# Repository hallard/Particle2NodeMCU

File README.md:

Particle Spark/Photon to NodeMCU Adapter
========================================

This adapter is used to put in place of a Spark/Photon a NodeMCU board with ESP8266 I needed for a specific French [project][3]. I needed SPI for RFM69 Module with IRQ on ~~GPIO2~~ GPIO15 and SS on GPIO2 (see below why).
I choosed NodeMCU boards instead of ESP8266 because NodeMCU has all I needed on board, such as pullups, switches, USB power, 3/3V regulator, USB2Serial...

Since ESP8266 has less pin than Particle boards, only "classic" have been connected

- SPI Interface (GPIO12 to 14) GPIO15 is used for RFM69 IRQ
- I2C Interface (GPIO14 and GPIO5)
- Serial (GPIO1 and GPIO3)
- GPIO0 as free I/O (Flash button on NodeMCU)
- GPIO2 is used as Chip Select (SS) for RFM69
- GPIO16 as free I/O (LED and KEY on NodeMCU)

I discovered some issue with 1st design, see below :
- ESP8266 to boot correctly needs some pins at defined level, GPIO15 must be LOW and GPIO2 must be HIGH. Unfortunatlly with RFM69 connected as IRQ to GPIO2 and SS to GPIO15 it does not boot because RF69 pull it DIO IRQ to LOW, making GPIO2 LOW and ESP8266 not booting. The fix is to reverse the wiring, connect IRQ to GPIO15 and SS to GPIO2 (and do according changes in the code). 
- Teleinfo had some issue due to NodeMCU USB/Serial onboard converter that was in conflict and was killing RX signal coming from optocoupler. To avoid this I've put 2 inverters to have a correct RX Teleinfo signal coming to EMP8266. No Risk because on board RX Signal of NodeMCU has a 470 Ohm resistor in serial of this line. To avoid this may be we could use a ESP8266 without any USB/Serial adapteur such as a Adafruit [Huzzah][5] or Olimex [ESP8266 Dev][6]
- it really just to fit board adapter on Remora if you have the big relay installed, it fits but it's really really close, so in version 1.1a, I just moved a little bit the adapter from the board relay.
- to be able to handle future Remora PCB version I added the feature to enable/disable Téléinfo FET Staging (they will already be placed on Remora V1.3 PCB) using Jumper J1 & J2.

This page has been updated to reflect the changes and the PCB also, it's now v1.1a.   

*Boards are still in progress, I did not fully tested them yet, I will update as soon has I got them in my hands. Use at your own risks*

Detailed Description
====================

Look at the schematics for more informations.

### Schematic  

### Boards  
&nbsp;
&nbsp; 

If you have old version V1.0 PCB and a RFM69 attached, here the fix, cut line in red and solder wire on green line.   

&nbsp;
&nbsp; 

You can order the PCB of this board v1.1a at [OSHPARK][4]

### Assembled boards

~~I'm currently waiting for boards from OSHPARK~~
Boards arrived, still testing before ordering V1.1a boards

##License

You can do whatever you like with this design.

##Misc
See news and other projects on my [blog][2] 
 
[2]: https://hallard.me
[3]: https://github.com/thibdct/programmateur-fil-pilote-wifi/tree/master/Logiciel/remora
[4]: https://oshpark.com/shared_projects/jYm6pI7a
[5]: https://www.adafruit.com/product/2471
[6]: https://www.olimex.com/Products/IoT/MOD-WIFI-ESP8266-DEV/

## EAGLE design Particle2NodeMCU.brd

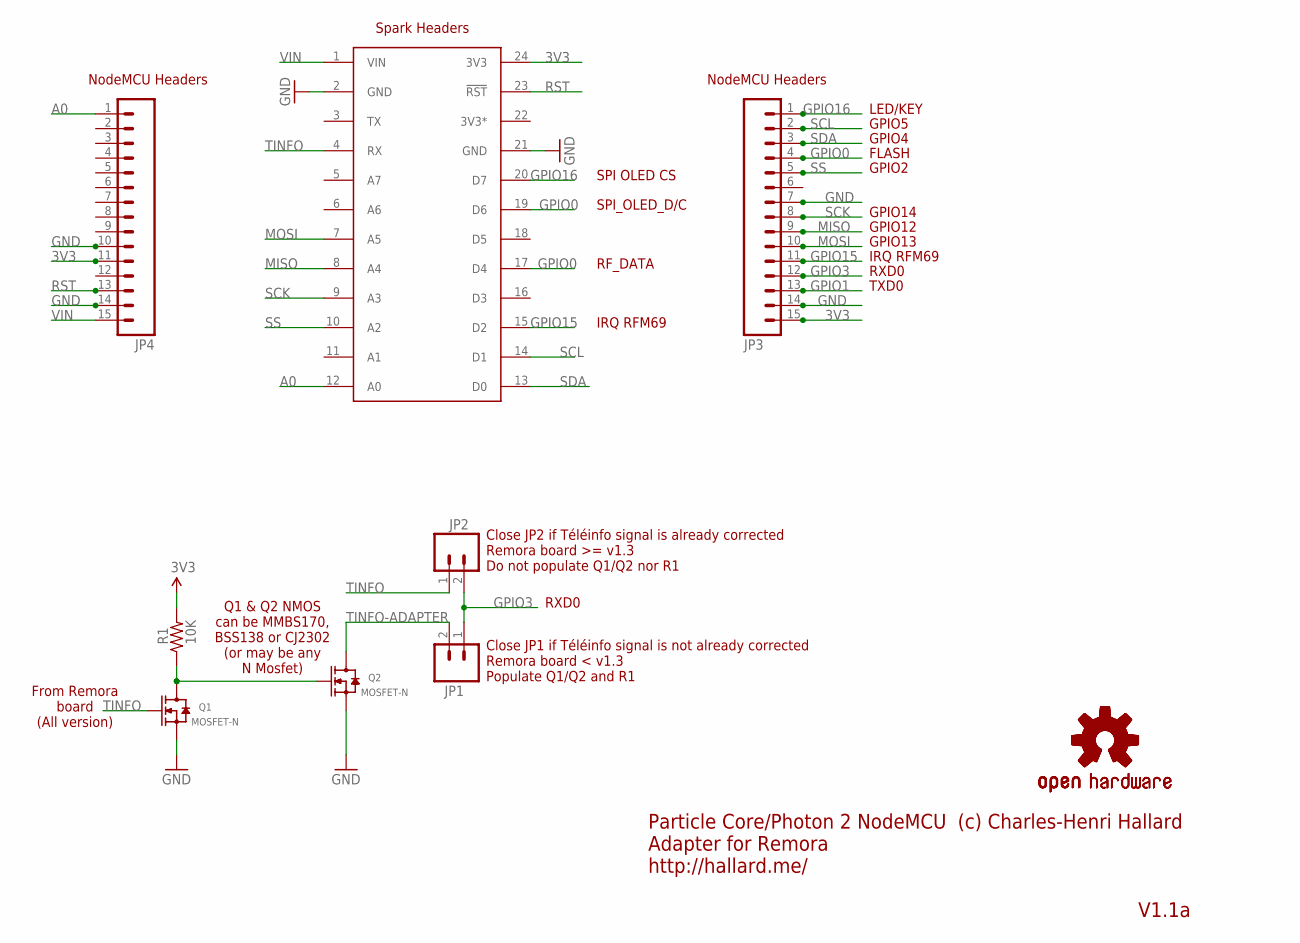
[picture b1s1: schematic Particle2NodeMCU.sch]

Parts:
JP1, JP2: M02LOCK; 1X02_LOCK
JP3, JP4: M15; 1X15
LOGO1, LOGO2: OSHW-LOGOM; OSHW-LOGO-M
Q1, Q2: MOSFET-N; SOT23
R1: 10K; 0805-RES
U$2: SPARK_CORECORE; SPARK_CORE

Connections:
3V3: JP3.15, JP4.11, R1.2, U$2.24 (3V3)
3V3*: U$2.22 (3V3*)
A0: JP4.1, U$2.12 (A0)
GND: JP3.7, JP3.14, JP4.10, JP4.14, Q1.2 (S), Q2.2 (S), U$2.2 (GND), U$2.21 (GND)
GPIO0: JP3.4, U$2.17 (D4), U$2.19 (D6)
GPIO1: JP3.13
GPIO3: JP1.1, JP2.2, JP3.12
GPIO15: JP3.11, U$2.15 (D2)
GPIO16: JP3.1, U$2.20 (D7)
MISO: JP3.9, U$2.8 (A4)
MOSI: JP3.10, U$2.7 (A5)
unnamed: Q1.3 (D), Q2.1 (G), R1.1
RST: JP4.13, U$2.23 (!RST)
SCK: JP3.8, U$2.9 (A3)
SCL: JP3.2, U$2.14 (D1)
SDA: JP3.3, U$2.13 (D0)
SS: JP3.5, U$2.10 (A2)
TINFO: JP2.1, Q1.1 (G), U$2.4 (RX)
TINFO-ADAPTER: JP1.2, Q2.3 (D)
VIN: JP4.15, U$2.1 (VIN)

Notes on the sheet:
IRQ RFM69
FLASH
GPIO12
GPIO4
GPIO5
RXD0
TXD0
GPIO13
GPIO14
GPIO2
LED/KEY
NodeMCU Headers
SPI_OLED_D/C
SPI OLED CS
RF_DATA
Spark Headers
Particle Core/Photon 2 NodeMCU Adapter for Remora http://hallard.me/
(c) Charles-Henri Hallard
V1.1a
Q1 & Q2 NMOS can be MMBS170, BSS138 or CJ2302 (or may be any N Mosfet)
Close JP1 if Téléinfo signal is not already corrected Remora board < v1.3 Populate Q1/Q2 and R1
Close JP2 if Téléinfo signal is already corrected Remora board >= v1.3 Do not populate Q1/Q2 nor R1
From Remora board (All version)

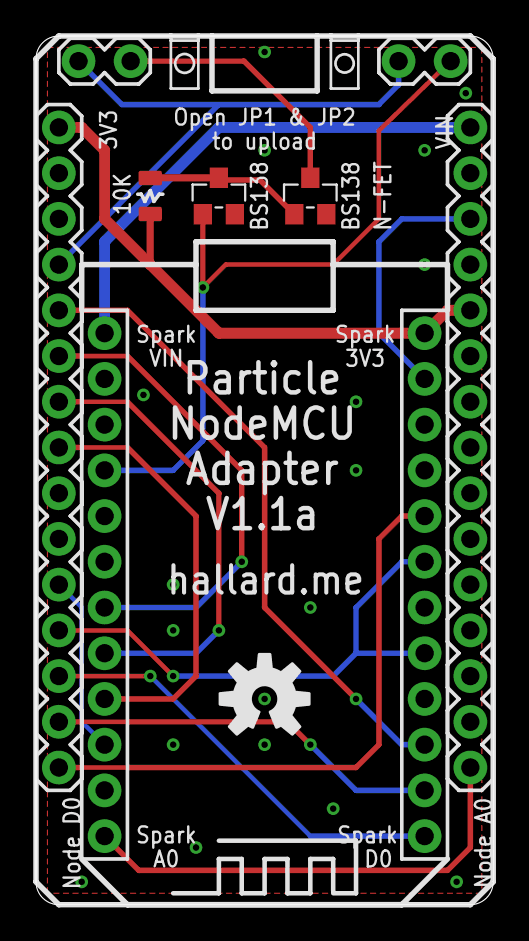
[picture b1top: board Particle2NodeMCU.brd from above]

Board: 2 copper layers, 25.4 x 48.3 mm, 10 parts (1 on the bottom side), 18 nets.

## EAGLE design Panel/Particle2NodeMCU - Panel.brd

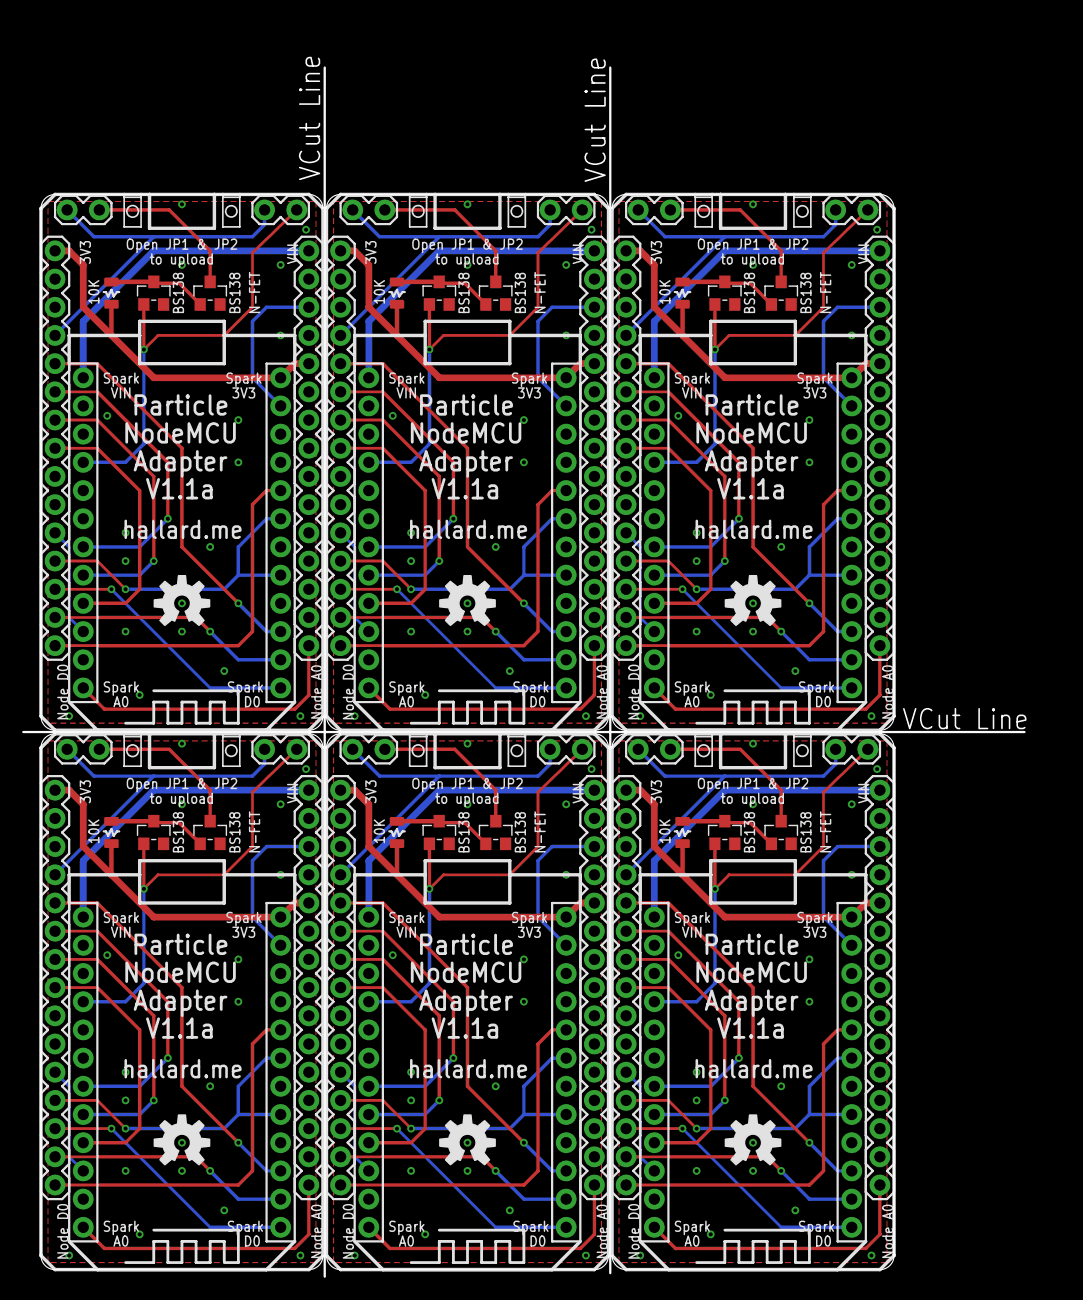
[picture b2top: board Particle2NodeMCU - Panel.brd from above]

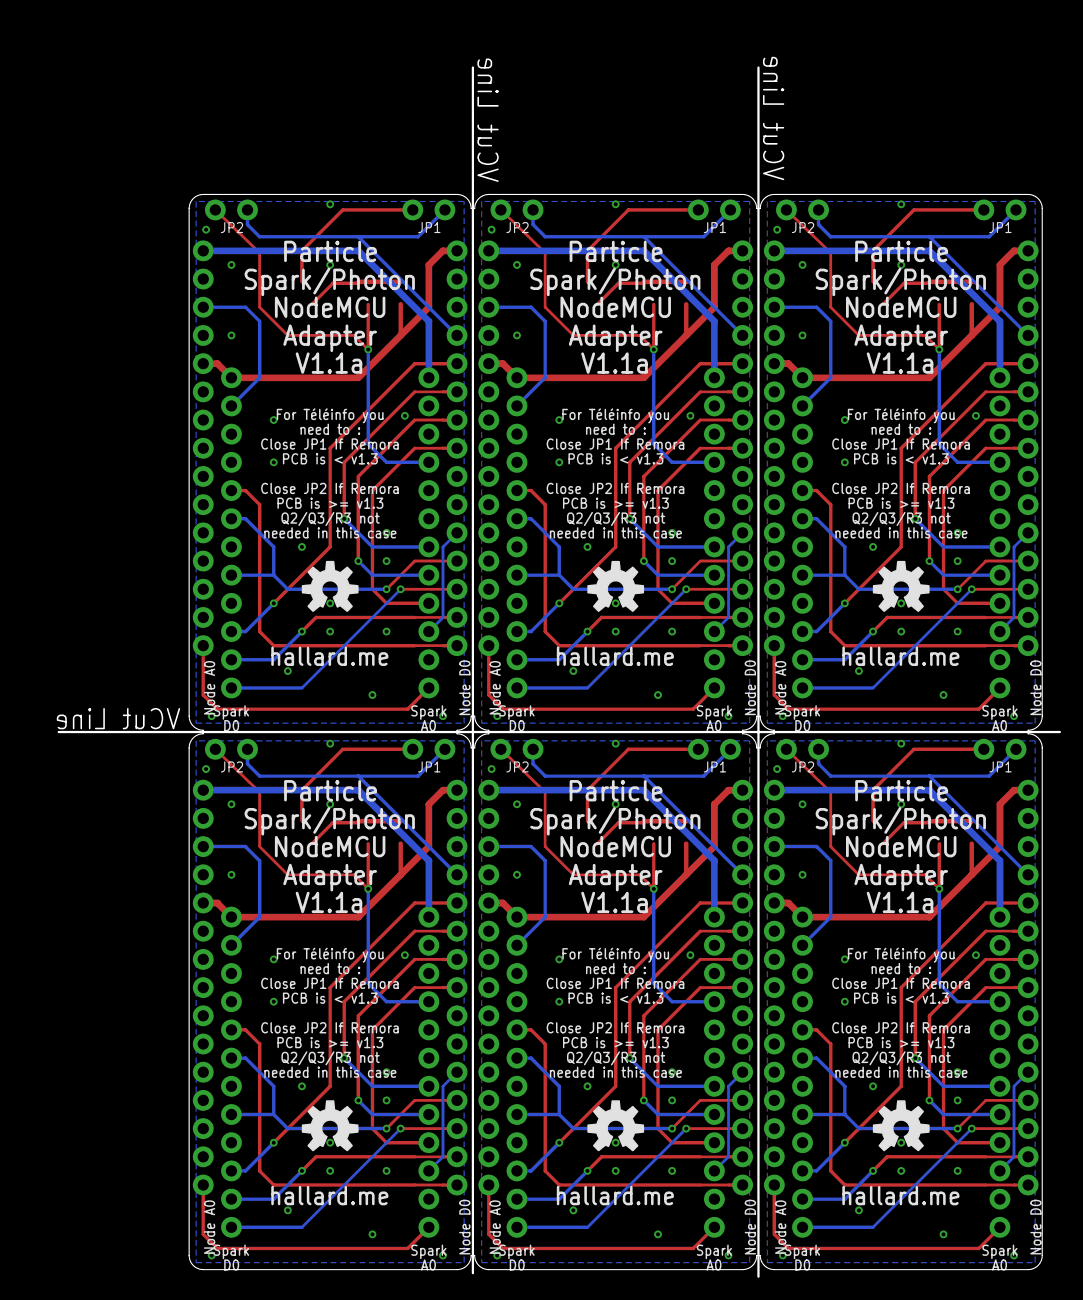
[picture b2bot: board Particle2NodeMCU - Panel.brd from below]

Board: 2 copper layers, 93.4 x 112.9 mm, 60 parts (6 on the bottom side), 108 nets.

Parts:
JP1, JP2, JP5, JP8, JP9, JP12, JP13, JP16, JP17, JP20, JP21, JP24: 1X02_LOCK
JP3, JP4, JP6, JP7, JP10, JP11, JP14, JP15, JP18, JP19, JP22, JP23: 1X15
LOGO1, LOGO2, LOGO3, LOGO4, LOGO5, LOGO6, LOGO7, LOGO8, LOGO9, LOGO10, LOGO11, LOGO12: OSHW-LOGOM; OSHW-LOGO-M
Q1, Q2, Q3, Q4, Q5, Q6, Q7, Q8, Q9, Q10, Q11, Q12: MOSFET-N; SOT23
R1, R2, R3, R4, R5, R6: 10K; 0805-RES
U$1, U$2, U$3, U$4, U$5, U$6: SPARK_CORECORE; SPARK_CORE

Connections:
3V1: JP6.11, JP7.15, R2.2, U$1.24
3V2: JP10.11, JP11.15, R3.2, U$3.24
3V3: JP3.15, JP4.11, R1.2, U$2.24
3V4: JP14.11, JP15.15, R4.2, U$4.24
3V5: JP18.11, JP19.15, R5.2, U$5.24
3V6: JP22.11, JP23.15, R6.2, U$6.24
A0: JP4.1, U$2.12
A1: JP6.1, U$1.12
A2: JP10.1, U$3.12
A3: JP14.1, U$4.12
A4: JP18.1, U$5.12
A5: JP22.1, U$6.12
GND: JP3.7, JP3.14, JP4.10, JP4.14, Q1.2, Q2.2, U$2.2, U$2.21
GND1: JP6.10, JP6.14, JP7.7, JP7.14, Q3.2, Q4.2, U$1.2, U$1.21
GND2: JP10.10, JP10.14, JP11.7, JP11.14, Q5.2, Q6.2, U$3.2, U$3.21
GND3: JP14.10, JP14.14, JP15.7, JP15.14, Q7.2, Q8.2, U$4.2, U$4.21
GND4: JP18.10, JP18.14, JP19.7, JP19.14, Q9.2, Q10.2, U$5.2, U$5.21
GND5: JP22.10, JP22.14, JP23.7, JP23.14, Q11.2, Q12.2, U$6.2, U$6.21
GPIO0: JP3.4, U$2.17, U$2.19
GPIO2: JP7.1, U$1.20
GPIO3: JP1.1, JP2.2, JP3.12
GPIO5: JP5.1, JP7.12, JP8.2
GPIO6: JP7.11, U$1.15
GPIO7: JP7.4, U$1.17, U$1.19
GPIO8: JP11.1, U$3.20
GPIO10: JP9.1, JP11.12, JP12.2
GPIO11: JP11.11, U$3.15
GPIO12: JP11.4, U$3.17, U$3.19
GPIO13: JP15.1, U$4.20
GPIO15: JP3.11, U$2.15
GPIO16: JP3.1, U$2.20
GPIO17: JP13.1, JP15.12, JP16.2
GPIO18: JP15.11, U$4.15
GPIO19: JP15.4, U$4.17, U$4.19
GPIO20: JP19.1, U$5.20
GPIO22: JP17.1, JP19.12, JP20.2
GPIO23: JP19.11, U$5.15
GPIO24: JP19.4, U$5.17, U$5.19
GPIO25: JP23.1, U$6.20
GPIO27: JP21.1, JP23.12, JP24.2
GPIO28: JP23.11, U$6.15
GPIO29: JP23.4, U$6.17, U$6.19
MISO: JP3.9, U$2.8
MISO1: JP7.9, U$1.8
MISO2: JP11.9, U$3.8
MISO3: JP15.9, U$4.8
MISO4: JP19.9, U$5.8
MISO5: JP23.9, U$6.8
MOSI: JP3.10, U$2.7
MOSI1: JP7.10, U$1.7
MOSI2: JP11.10, U$3.7
MOSI3: JP15.10, U$4.7
MOSI4: JP19.10, U$5.7
MOSI5: JP23.10, U$6.7
unnamed: Q3.3, Q4.1, R2.1
unnamed: Q5.3, Q6.1, R3.1
unnamed: Q1.3, Q2.1, R1.1
unnamed: Q7.3, Q8.1, R4.1
unnamed: Q9.3, Q10.1, R5.1
unnamed: Q11.3, Q12.1, R6.1
RST: JP4.13, U$2.23
RST1: JP6.13, U$1.23
RST2: JP10.13, U$3.23
RST3: JP14.13, U$4.23
RST4: JP18.13, U$5.23
RST5: JP22.13, U$6.23
SCK: JP3.8, U$2.9
SCK1: JP7.8, U$1.9
SCK2: JP11.8, U$3.9
SCK3: JP15.8, U$4.9
SCK4: JP19.8, U$5.9
SCK5: JP23.8, U$6.9
SCL: JP3.2, U$2.14
SCL1: JP7.2, U$1.14
SCL2: JP11.2, U$3.14
SCL3: JP15.2, U$4.14
SCL4: JP19.2, U$5.14
SCL5: JP23.2, U$6.14
SDA: JP3.3, U$2.13
SDA1: JP7.3, U$1.13
SDA2: JP11.3, U$3.13
SDA3: JP15.3, U$4.13
SDA4: JP19.3, U$5.13
SDA5: JP23.3, U$6.13
SS: JP3.5, U$2.10
SS1: JP7.5, U$1.10
SS2: JP11.5, U$3.10
SS3: JP15.5, U$4.10
SS4: JP19.5, U$5.10
SS5: JP23.5, U$6.10
TINFO: JP2.1, Q1.1, U$2.4
TINFO1: JP8.1, Q3.1, U$1.4
TINFO2: JP12.1, Q5.1, U$3.4
TINFO3: JP16.1, Q7.1, U$4.4
TINFO4: JP20.1, Q9.1, U$5.4
TINFO5: JP24.1, Q11.1, U$6.4
TINFO-ADAPTER: JP1.2, Q2.3
TINFO-ADAPTER1: JP5.2, Q4.3
TINFO-ADAPTER2: JP9.2, Q6.3
TINFO-ADAPTER3: JP13.2, Q8.3
TINFO-ADAPTER4: JP17.2, Q10.3
TINFO-ADAPTER5: JP21.2, Q12.3
VIN: JP4.15, U$2.1
VIN1: JP6.15, U$1.1
VIN2: JP10.15, U$3.1
VIN3: JP14.15, U$4.1
VIN4: JP18.15, U$5.1
VIN5: JP22.15, U$6.1

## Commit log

2015-08-27 :tada: Added .gitattributes & .gitignore files
2015-08-27 Creation
2015-08-27 Création
2015-08-27 Updated schematic picture title
2015-08-27 Added OSHPark Link
2015-09-27 Fixed GPIO now version 1.0a
2015-09-27 Fix Typo
2015-09-27 Updated text
2015-09-27 Relay fix explannation
2015-09-27 Fixed Wiring Error
2015-09-28 Version 1.1 ajout inverseur FET
2015-09-28 Silk Error on R1
2015-10-04 Updated to 1.1a
2015-10-04 OSHPark Link vor v1.1a
2015-10-04 Approved errors
2015-10-06 Label error on GPIO2/GPIO15
2015-10-22 Ready To Panelize
2015-10-22 Folder Reorg

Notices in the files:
parts and their libraries:
SparkFun-Connectors: Licensing: Creative Commons ShareAlike 4.0 International - https://creativecommons.org/licenses/by-sa/4.0
